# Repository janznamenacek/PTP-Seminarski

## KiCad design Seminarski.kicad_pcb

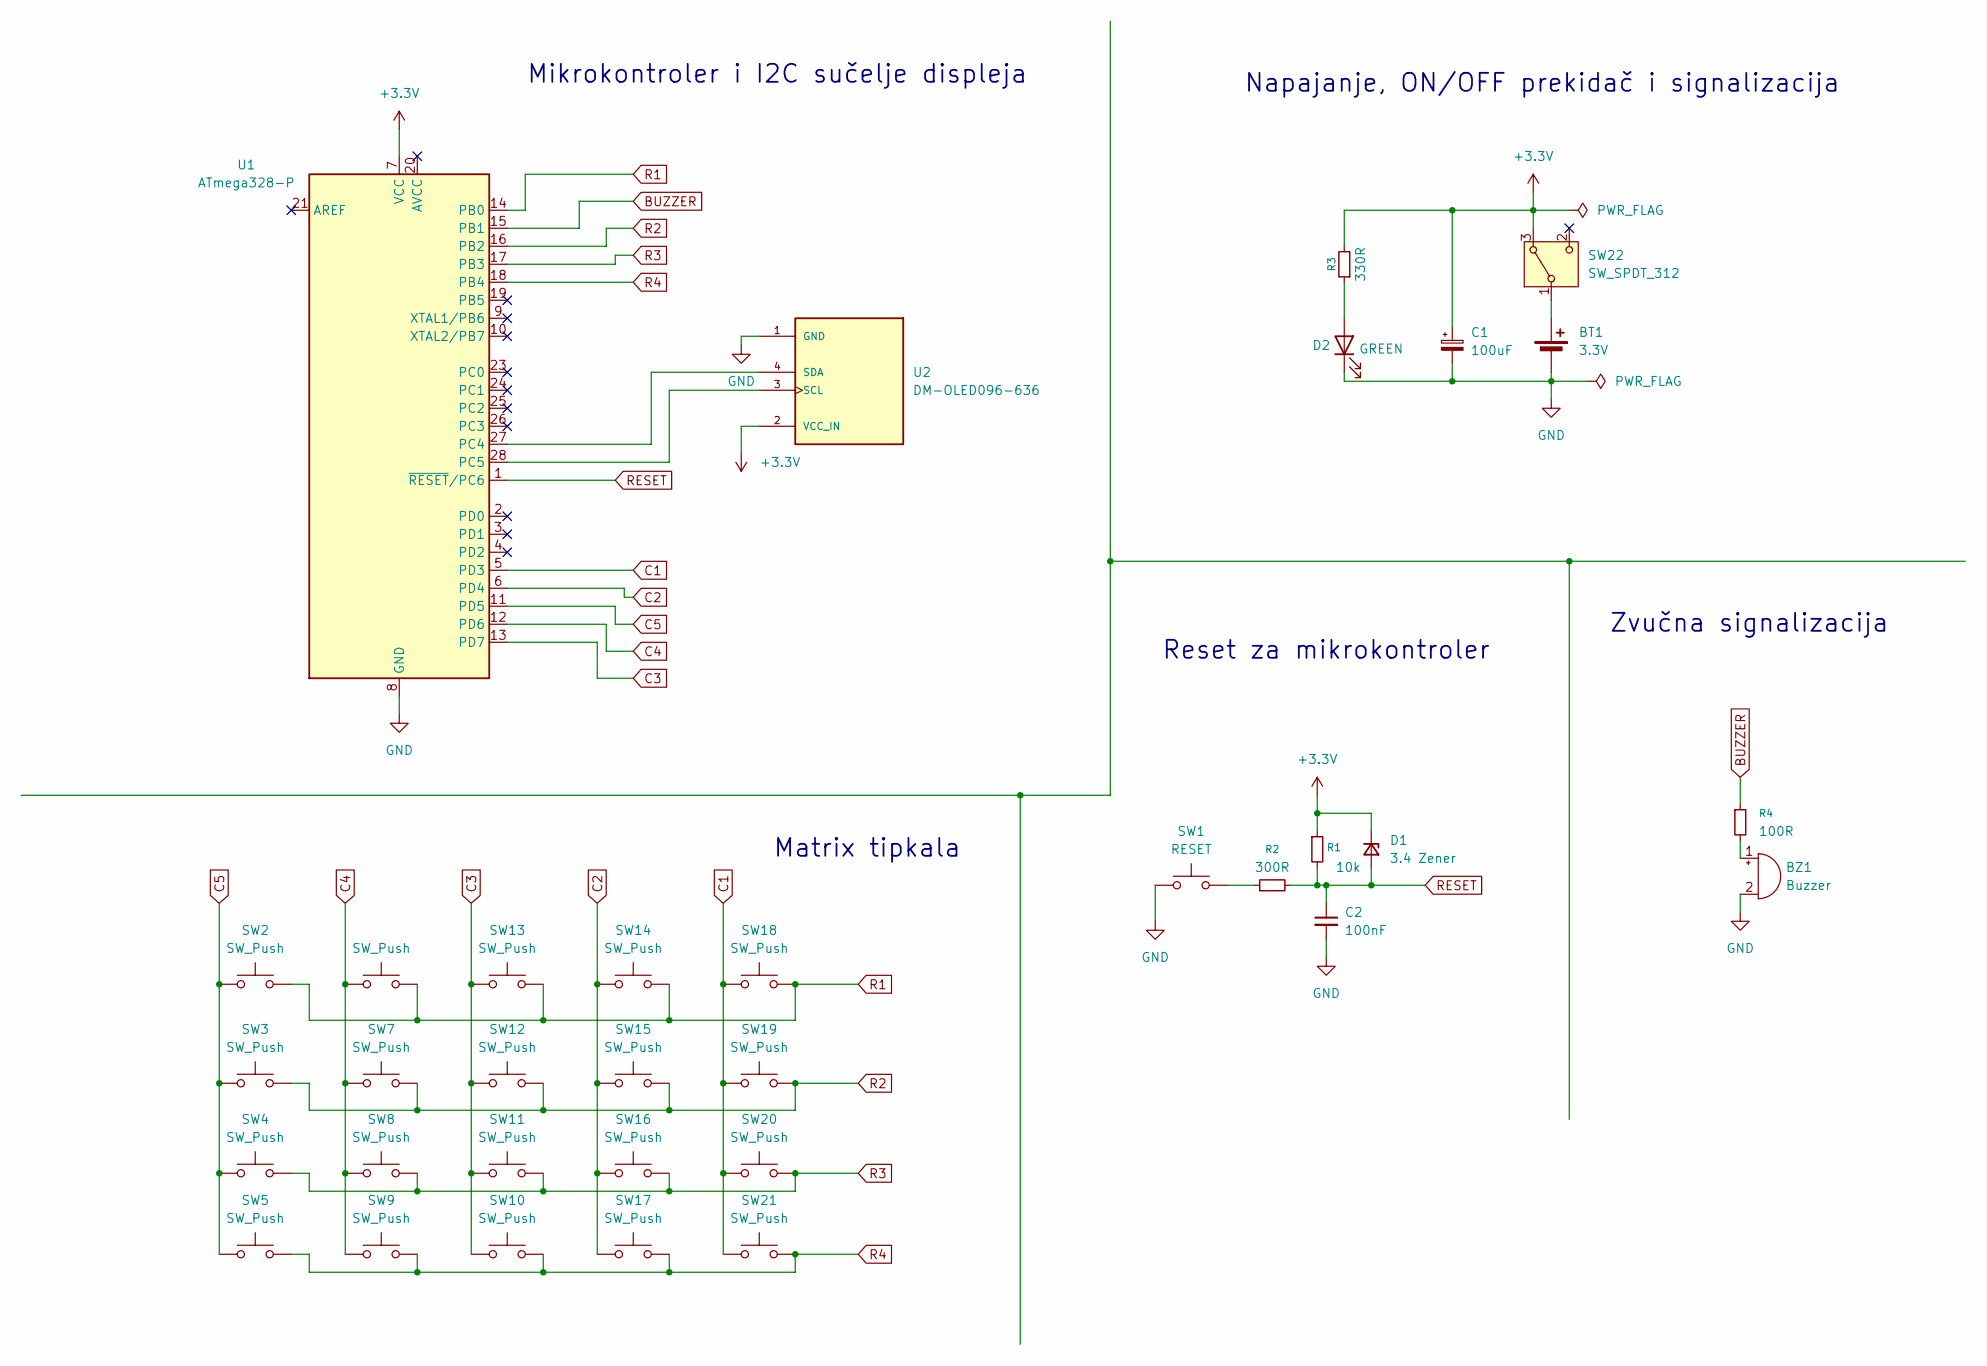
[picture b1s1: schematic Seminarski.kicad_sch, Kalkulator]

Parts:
BT1: 3.3V; BatteryHolder_Keystone_1060_1x2032; ManufacturerPartNumber 1060
BZ1: Buzzer; Buzzer_TDK_PS1240P02BT_D12.2mm_H6.5mm; ManufacturerPartNumber CMT-9605-85T
C1: 100uF; CP_Radial_D5.0mm_P2.50mm; ManufacturerPartNumber ECEA0JKA101I
C2: 100nF; C_1206_3216Metric; ManufacturerPartNumber CL31B104KBCNNNC
D1: 3.4 Zener; D_SOD-323F; ManufacturerPartNumber MM3Z3V3T1G
D2: GREEN; LED_2010_5025Metric_Pad1.52x2.65mm_HandSolder; ManufacturerPartNumber ELSH-F71G1-0LPNM-CG1G2
R1: 10k; R_1206_3216Metric; ManufacturerPartNumber 1206S4F1002T5E
R2: 300R; R_1206_3216Metric; ManufacturerPartNumber 1206S4F3000T5E
R3: 330R; R_1206_3216Metric; ManufacturerPartNumber 1206S4J0331T5E
R4: 100R; R_1206_3216Metric; ManufacturerPartNumber 1206S4J0101T5E
SW1: RESET; SW_Push_1P1T_NO_E-Switch_TL3301NxxxxxG; ManufacturerPartNumber TSS 61 R
SW2, SW3, SW4, SW5, SW6, SW7, SW8, SW9, SW10, SW11, SW12, SW13, SW14, SW15, SW16, SW17, SW18, SW19, SW20, SW21: SW_Push; SW_Push_1P1T_NO_E-Switch_TL3301NxxxxxG; ManufacturerPartNumber TSS 62 N
SW22: SW_SPDT_312; SW_Slide_SPDT_Angled_CK_OS102011MA1Q; ManufacturerPartNumber OS102011MA1QN1C
U1: ATmega328-P; DIP-28_W7.62mm; ManufacturerPartNumber ATMEGA328P-PU
U2: DM-OLED096-636; MODULE_DM-OLED096-636; PARTREV 2018-09-10

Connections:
+3.3V: C1.1, D1.1 (K), R1.1, R3.2, SW22.3 (A), U1.7 (VCC), U2.2 (VCC_IN)
BUZZER: R4.1, U1.15 (PB1)
C1: SW18.1, SW19.1, SW20.1, SW21.1, U1.5 (PD3)
C2: SW14.1, SW15.1, SW16.1, SW17.1, U1.6 (PD4)
C3: SW10.1, SW11.1, SW12.1, SW13.1, U1.13 (PD7)
C4: SW6.1, SW7.1, SW8.1, SW9.1, U1.12 (PD6)
C5: SW2.1, SW3.1, SW4.1, SW5.1, U1.11 (PD5)
GND: BT1.2 (-), BZ1.2 (-), C1.2, C2.2, D2.1 (K), SW1.1, U1.8 (GND), U1.22 (GND), U2.1 (GND)
unnamed: BT1.1 (+), SW22.1 (B)
unnamed: BZ1.1 (+), R4.2
unnamed: D2.2 (A), R3.1
unnamed: R2.1, SW1.2
unnamed: U1.27 (PC4), U2.4 (SDA)
unnamed: U1.28 (PC5), U2.3 (SCL)
R1: SW2.2, SW6.2, SW13.2, SW14.2, SW18.2, U1.14 (PB0)
R2: SW3.2, SW7.2, SW12.2, SW15.2, SW19.2, U1.16 (PB2)
R3: SW4.2, SW8.2, SW11.2, SW16.2, SW20.2, U1.17 (PB3)
R4: SW5.2, SW9.2, SW10.2, SW17.2, SW21.2, U1.18 (PB4)
RESET: C2.1, D1.2 (A), R1.2, R2.2, U1.1 (~RESET/PC6)

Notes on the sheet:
Mikrokontroler i I2C sučelje displeja
Reset za mikrokontroler
Zvučna signalizacija
Napajanje, ON/OFF prekidač i signalizacija
Matrix tipkala

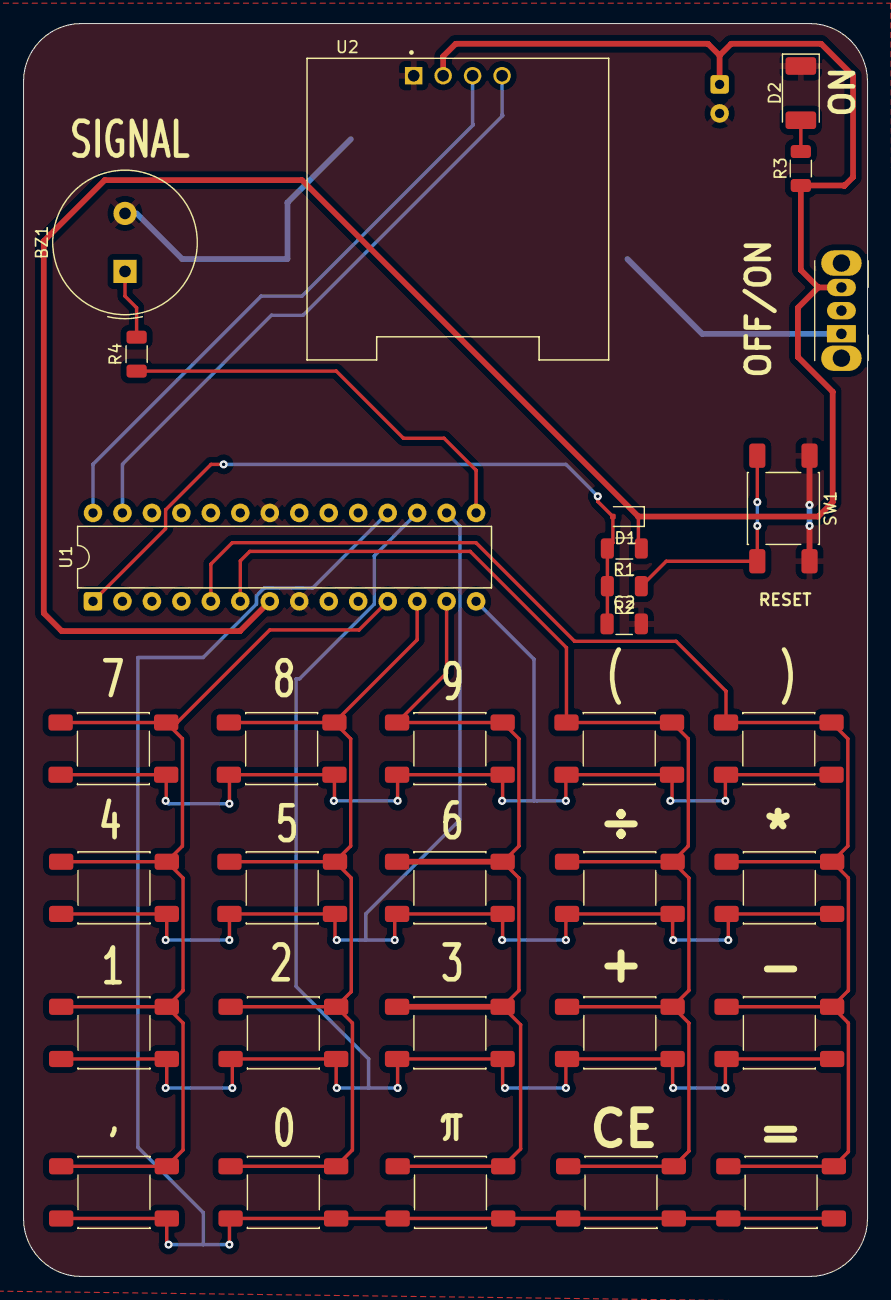
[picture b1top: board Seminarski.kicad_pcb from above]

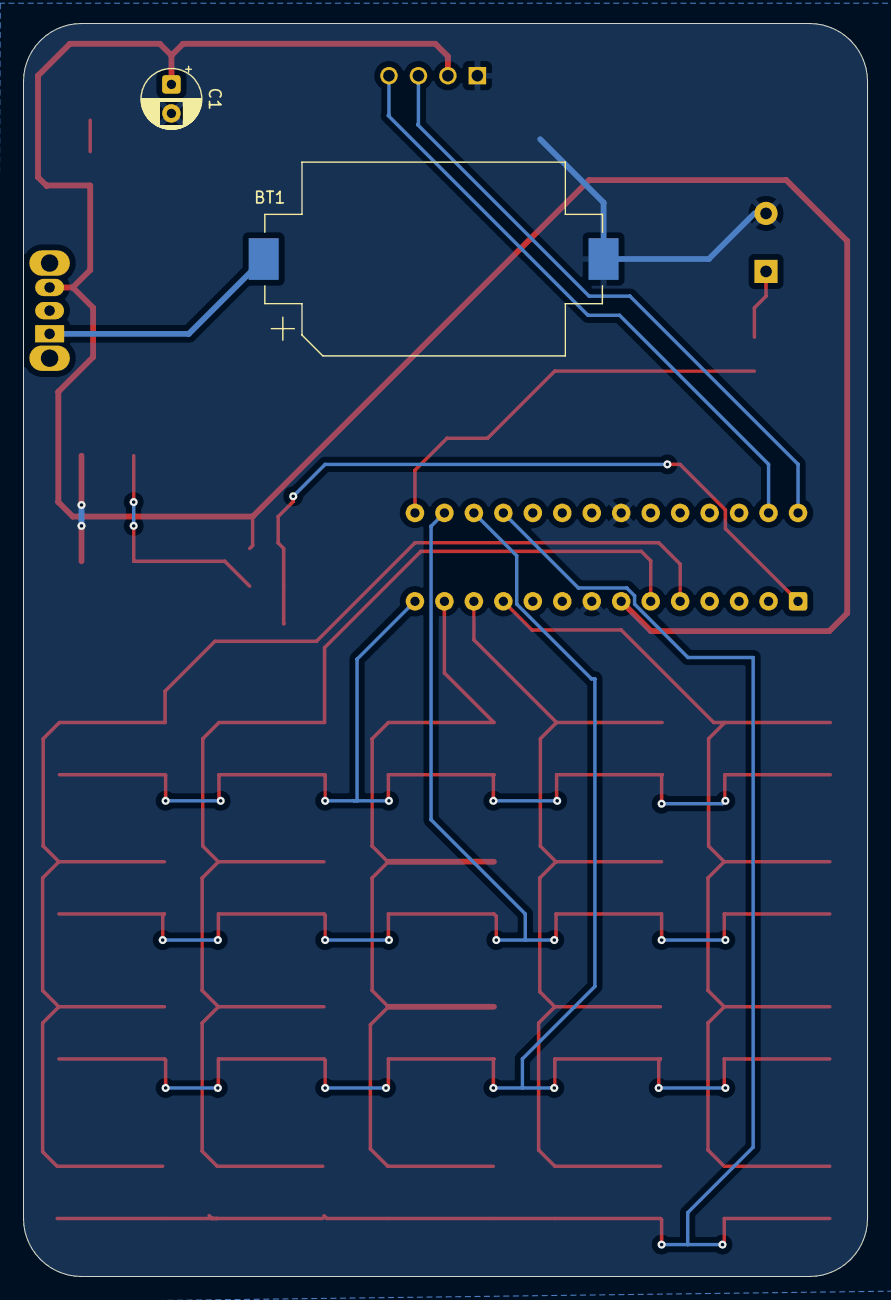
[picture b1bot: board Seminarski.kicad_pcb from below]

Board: 2 copper layers, 72.8 x 108.0 mm, 34 parts (2 on the bottom side), 19 nets.

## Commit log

2026-01-12 V1.0
2026-01-20 Veci display
2026-01-25 Final
